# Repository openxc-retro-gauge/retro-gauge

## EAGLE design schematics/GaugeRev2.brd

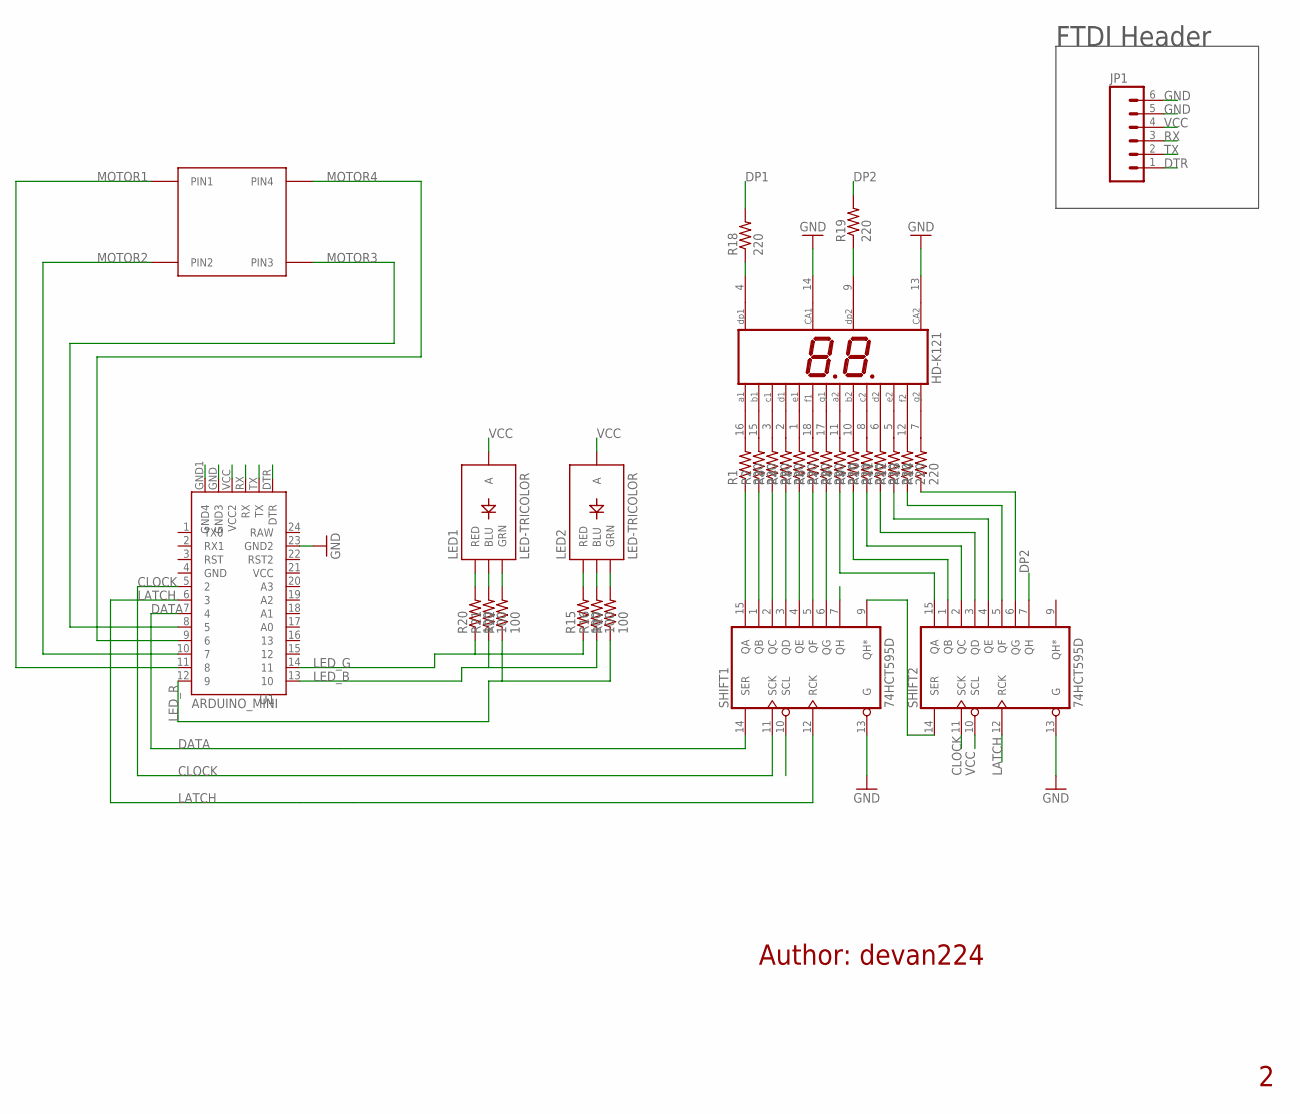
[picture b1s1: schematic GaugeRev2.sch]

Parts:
DIS2: HD-K121; HDSP-R
JP1: M06SIP; 1X06
LED1, LED2: LED-TRICOLOR; LED-TRICOLOR-SMD
R1, R2, R3, R4, R5, R6, R7, R8, R9, R10, R11, R12, R13, R14, R18, R19: 220; R1206
R15, R16, R17, R20, R21, R22: 100; R1206
SHIFT1, SHIFT2: 74HCT595D; SO16
U1: ARDUINO_MINI
U2: VID29

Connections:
1: DIS2.4 (DP1), R18.1
2: DIS2.9 (DP2), R19.1
A1: R1.1, SHIFT1.15 (QA)
A2: R8.1, SHIFT2.15 (QA)
B1: R2.1, SHIFT1.1 (QB)
B2: R9.1, SHIFT2.1 (QB)
C1: R3.1, SHIFT1.2 (QC)
CLOCK: SHIFT1.11 (SCK), SHIFT2.11 (SCK), U1.5 (2)
D1: R4.1, SHIFT1.3 (QD)
DATA: SHIFT1.14 (SER), U1.7 (4)
DP1: R18.2, SHIFT1.7 (QH)
DP2: R19.2, SHIFT2.7 (QH)
DTR: JP1.1, U1.DTR
E1: R5.1, SHIFT1.4 (QE)
F1: R6.1, SHIFT1.5 (QF)
G1: R7.1, SHIFT1.6 (QG)
G2: R14.1, SHIFT2.6 (QG)
GND: DIS2.13 (CA2), DIS2.14 (CA1), JP1.5, JP1.6, SHIFT1.8 (GND), SHIFT1.13 (G), SHIFT2.8 (GND), SHIFT2.13 (G), U1.23 (GND2), U1.GND (GND3), U1.GND1 (GND4)
LATCH: SHIFT1.12 (RCK), SHIFT2.12 (RCK), U1.6 (3)
LED_B: R16.1, R21.1, U1.13 (10)
LED_G: R15.1, R20.1, U1.14 (11)
LED_R: R17.1, R22.1, U1.12 (9)
MOTOR1: U1.11 (8), U2.PIN1
MOTOR2: U1.10 (7), U2.PIN2
MOTOR3: U1.8 (5), U2.PIN3
MOTOR4: U1.9 (6), U2.PIN4
unnamed: DIS2.16 (A1), R1.2
unnamed: DIS2.15 (B1), R2.2
unnamed: DIS2.3 (C1), R3.2
unnamed: DIS2.2 (D1), R4.2
unnamed: DIS2.1 (E1), R5.2
unnamed: DIS2.18 (F1), R6.2
unnamed: DIS2.17 (G1), R7.2
unnamed: DIS2.11 (A2), R8.2
unnamed: DIS2.10 (B2), R9.2
unnamed: DIS2.8 (C2), R10.2
unnamed: DIS2.6 (D2), R11.2
unnamed: DIS2.5 (E2), R12.2
unnamed: DIS2.12 (F2), R13.2
unnamed: DIS2.7 (G2), R14.2
unnamed: LED2.G (GRN), R17.2
unnamed: LED2.B (BLU), R16.2
unnamed: R10.1, SHIFT2.2 (QC)
unnamed: R11.1, SHIFT2.3 (QD)
unnamed: R12.1, SHIFT2.4 (QE)
unnamed: R13.1, SHIFT2.5 (QF)
unnamed: LED2.R (RED), R15.2
unnamed: LED1.G (GRN), R22.2
unnamed: LED1.B (BLU), R21.2
unnamed: LED1.R (RED), R20.2
Q*: SHIFT1.9 (QH*), SHIFT2.14 (SER)
RX: JP1.3, U1.RX
TX: JP1.2, U1.TX
VCC: JP1.4, LED1.A, LED2.A, SHIFT1.10 (SCL), SHIFT1.16 (VCC), SHIFT2.10 (SCL), SHIFT2.16 (VCC), U1.VCC (VCC2)

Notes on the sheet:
Author: devan224
FTDI Header

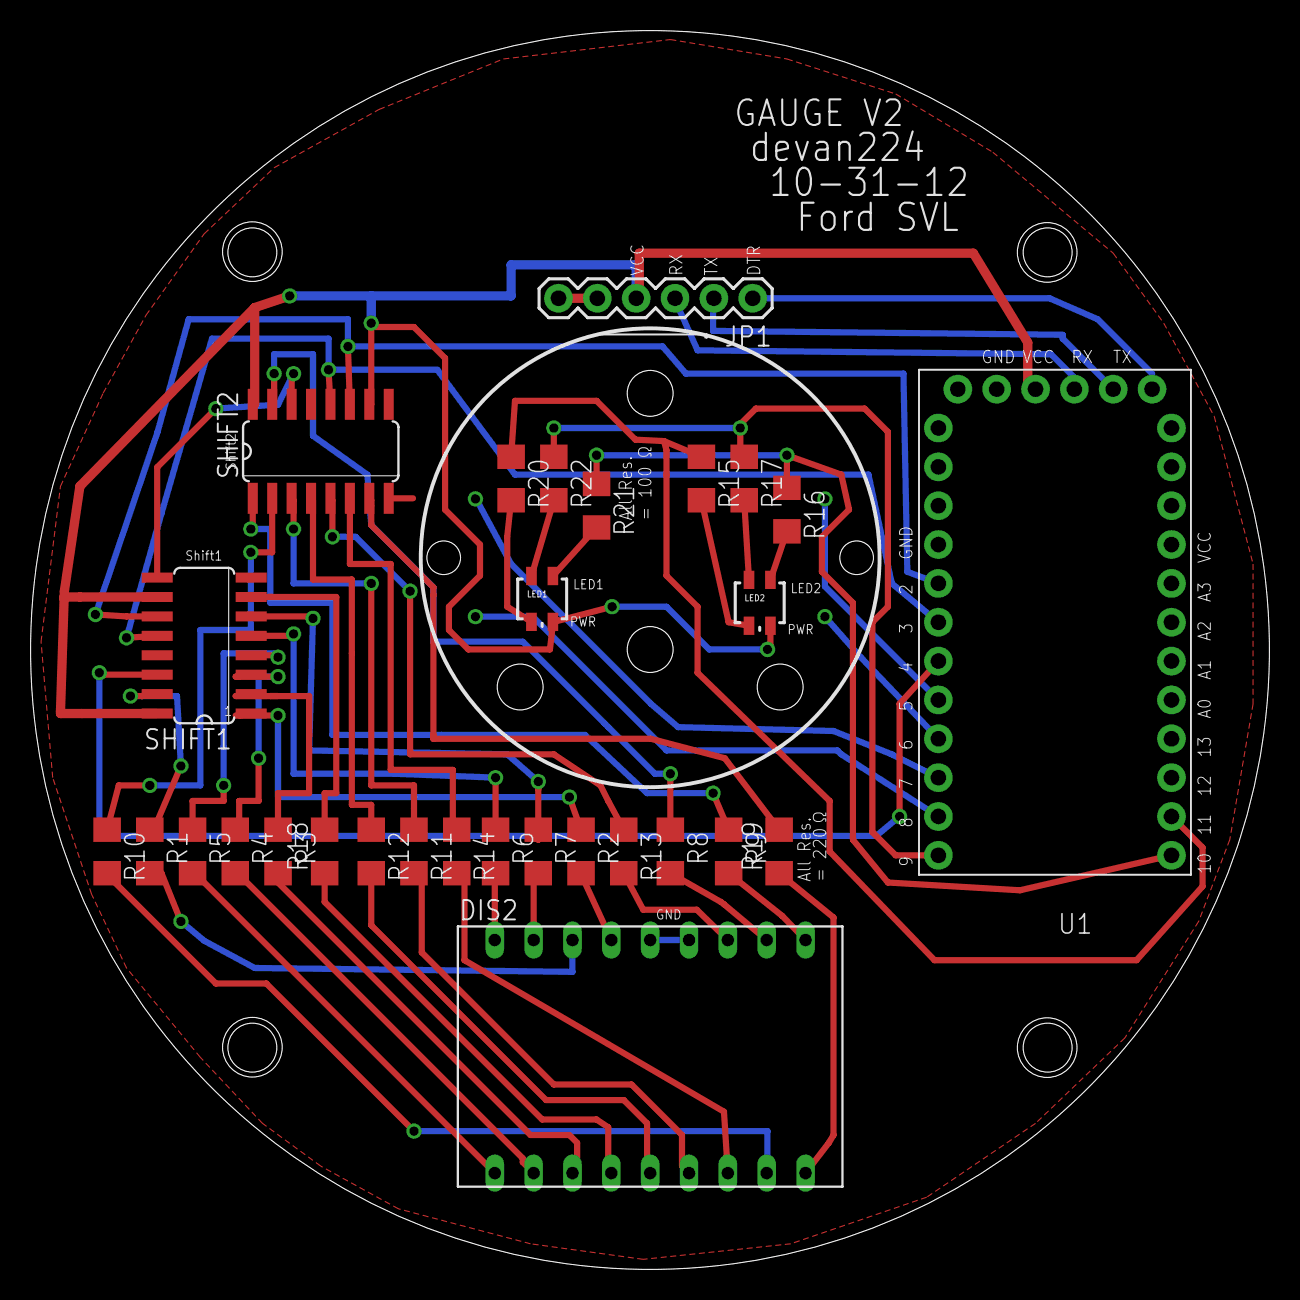
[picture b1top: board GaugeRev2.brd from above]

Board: 2 copper layers, 81.0 x 81.0 mm, 30 parts (0 on the bottom side), 54 nets.

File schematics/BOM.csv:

Partlist exported from /Users/evansda/Documents/eagle/retroGauge/Rev2/GaugeRev2.sch at 12/18/12 12:39 PM

Assembly variant: 

Qty Value        Device       Parts                                                                
1                M06SIP       JP1                                                                  
2   74HCT595D    74HCT595D    SHIFT1, SHIFT2                                                       
6   100          R-US_R1206   R15, R16, R17, R20, R21, R22                                         
16  220          R-US_R1206   R1, R2, R3, R4, R5, R6, R7, R8, R9, R10, R11, R12, R13, R14, R18, R19
1   ARDUINO_MINI ARDUINO_MINI U1                                                                   
1   HD-K121      HD-K121      DIS2                                                                 
2   LED-TRICOLOR LED-TRICOLOR LED1, LED2                                                           
1   VID29        VID29        U2

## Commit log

2013-01-09 Add enclosure step files and schematics.
2013-01-09 Add Android app and Arduino firmware for guage.
2013-01-09 Add BOM.
2013-01-09 Add README for overall project.
2013-01-09 Add BSD license file.
2013-01-09 Add Arduino README.
2013-01-09 Only put 1 space after periods.
2013-01-09 Typos.
2013-01-09 Fix library references.
2013-01-09 Add troubleshooting instructions for re-linking libraries in Eclipse.
2013-01-09 Add hardware license.
2013-01-10 Add docs on inner workings of Gauge Driver.
2013-01-17 Remove rtf version of gitignore.
2013-01-23 Bug fix: toggle switch is no longer reversed.
2013-02-06 Added a debug text view. Fixed the incorrect "Sending Updates" indicator.
2013-02-08 Adding VID29 datasheet
2013-04-17 adding MakerBot Friendly housings
2013-04-17 Updated BOM
2013-04-17 updated makerbot models
2013-04-18 adding .dxf file for creating Gauge Face
2013-04-19 Ignore Eagle backup files.
2013-04-24 Update README.mkd
    404 error on previous link
    Cheers, J
2013-04-24 adding instructables link on the README file and an updated BOM
2013-04-24 Pull firmware and android in from 'next'.
2013-04-25 adding makerbot file for printing
2013-04-26 added makerbot build file
2013-04-26 updated README file
2013-04-27 Don't version Eclipse settings.
2013-04-27 Declare that we use USB host feature.
2013-04-27 Avoid leaking a service connection.
2013-04-27 Replace tabs with 4 spaces.
2013-04-27 Ignore more Eclipse junk.
2013-04-27 Update target SDK to API 17.
2013-04-27 Connect device when attached.
2013-04-30 updating BOM
2013-05-14 fix openxcplatform.com link on README
2013-05-17 Made the speed, mpg, steering wheel angle, fuel, and odo thread safe.
2013-05-21 fix vendor ID for FTDI chip to 1027. make sure GaugeDriverActivity only launches once.
2013-05-28 Removed redundant USB permissions check, removed unused imports, removed unused ACTION_USB_DEVICE_ATTACHED handler.
2013-05-30 Fixed re-connection bug with multiple devices. Now handles device disconnects properly with multiple devices.
2013-07-12 Change hardware license to Creative Commons.
2013-07-12 Document the difference in the makerbot-friendly STL files.
2013-07-12 Move needle STL up a level since it's not MakerBot-specific.
2013-07-12 Note that the OpenXC fork of FTDriver is required.
2013-07-15 this commit is to add a new version of the needle to the repository
2013-07-18 Link to Switec X25 library directly.
2013-07-18 Add Makefile for firmware and re-organize functions.
2013-07-18 Resolve some compiler warnings when using the Makefile.
2013-07-18 Bump Arduino-Makefile.
2013-07-18 Fix board tag in Makefile.
2013-07-18 Add some basic docs on using Makefile.
2013-07-18 Move protocol tops to the top-level README.
2013-07-18 Document the correct baud rate.
2013-07-18 Move one android section back to the correct README.
2013-07-18 Update docs for flashing from Arduino.
2013-07-18 Use 5v Arduino Pro library to get the correct clock rate.
2013-07-18 Refactor code for clarity.
2013-07-18 Add a self-test routine to the startup procedure.
2013-07-18 Use more general path to openxc-android library in Eclipse project.
2013-07-18 Replace tabs with spaces, and a few other stylistic things.
2013-07-18 Remove commented out code.
2013-07-18 Start function names with lower case.
2013-07-18 Always use {} with if/else, even when only one line.
2013-07-18 Rename more class methods to start with lower case.
2013-07-18 Fix brace on if statement.
2013-07-18 Remove unused imports.
2013-07-18 Remove unused function.
2013-07-18 Use an existing method in upstream FTDriver to detach device.
2013-07-18 Fix all indendation in Java sources.
2013-07-18 Make member variables private and remove unused ones.
2013-07-18 Refactor main activity for clarity.
2013-07-22 Include SwitecX25 library in .ino to trigger Arduino library compilation.
2013-07-23 Refactor rolling average handler and clarify MPG calculation.
    This is seemingly a little more accurate, it just takes a little while to settle
    on the actual MPG and is susceptible to outliers.
2013-07-23 Grab SWA and speed synchronously to keep thing simple, since we're on a timer.
2013-07-26 Moved Updates Toggle set to onResume() after connection to fix incorrect toggle setting bug. Added Toast messages for gauge connections and disconnects.
2013-09-11 Leave a note that repo was split up.

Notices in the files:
parts and their libraries:
SparkFun: Licensing: CC v3.0 Share-Alike You are welcome to use this library for commercial purposes.
